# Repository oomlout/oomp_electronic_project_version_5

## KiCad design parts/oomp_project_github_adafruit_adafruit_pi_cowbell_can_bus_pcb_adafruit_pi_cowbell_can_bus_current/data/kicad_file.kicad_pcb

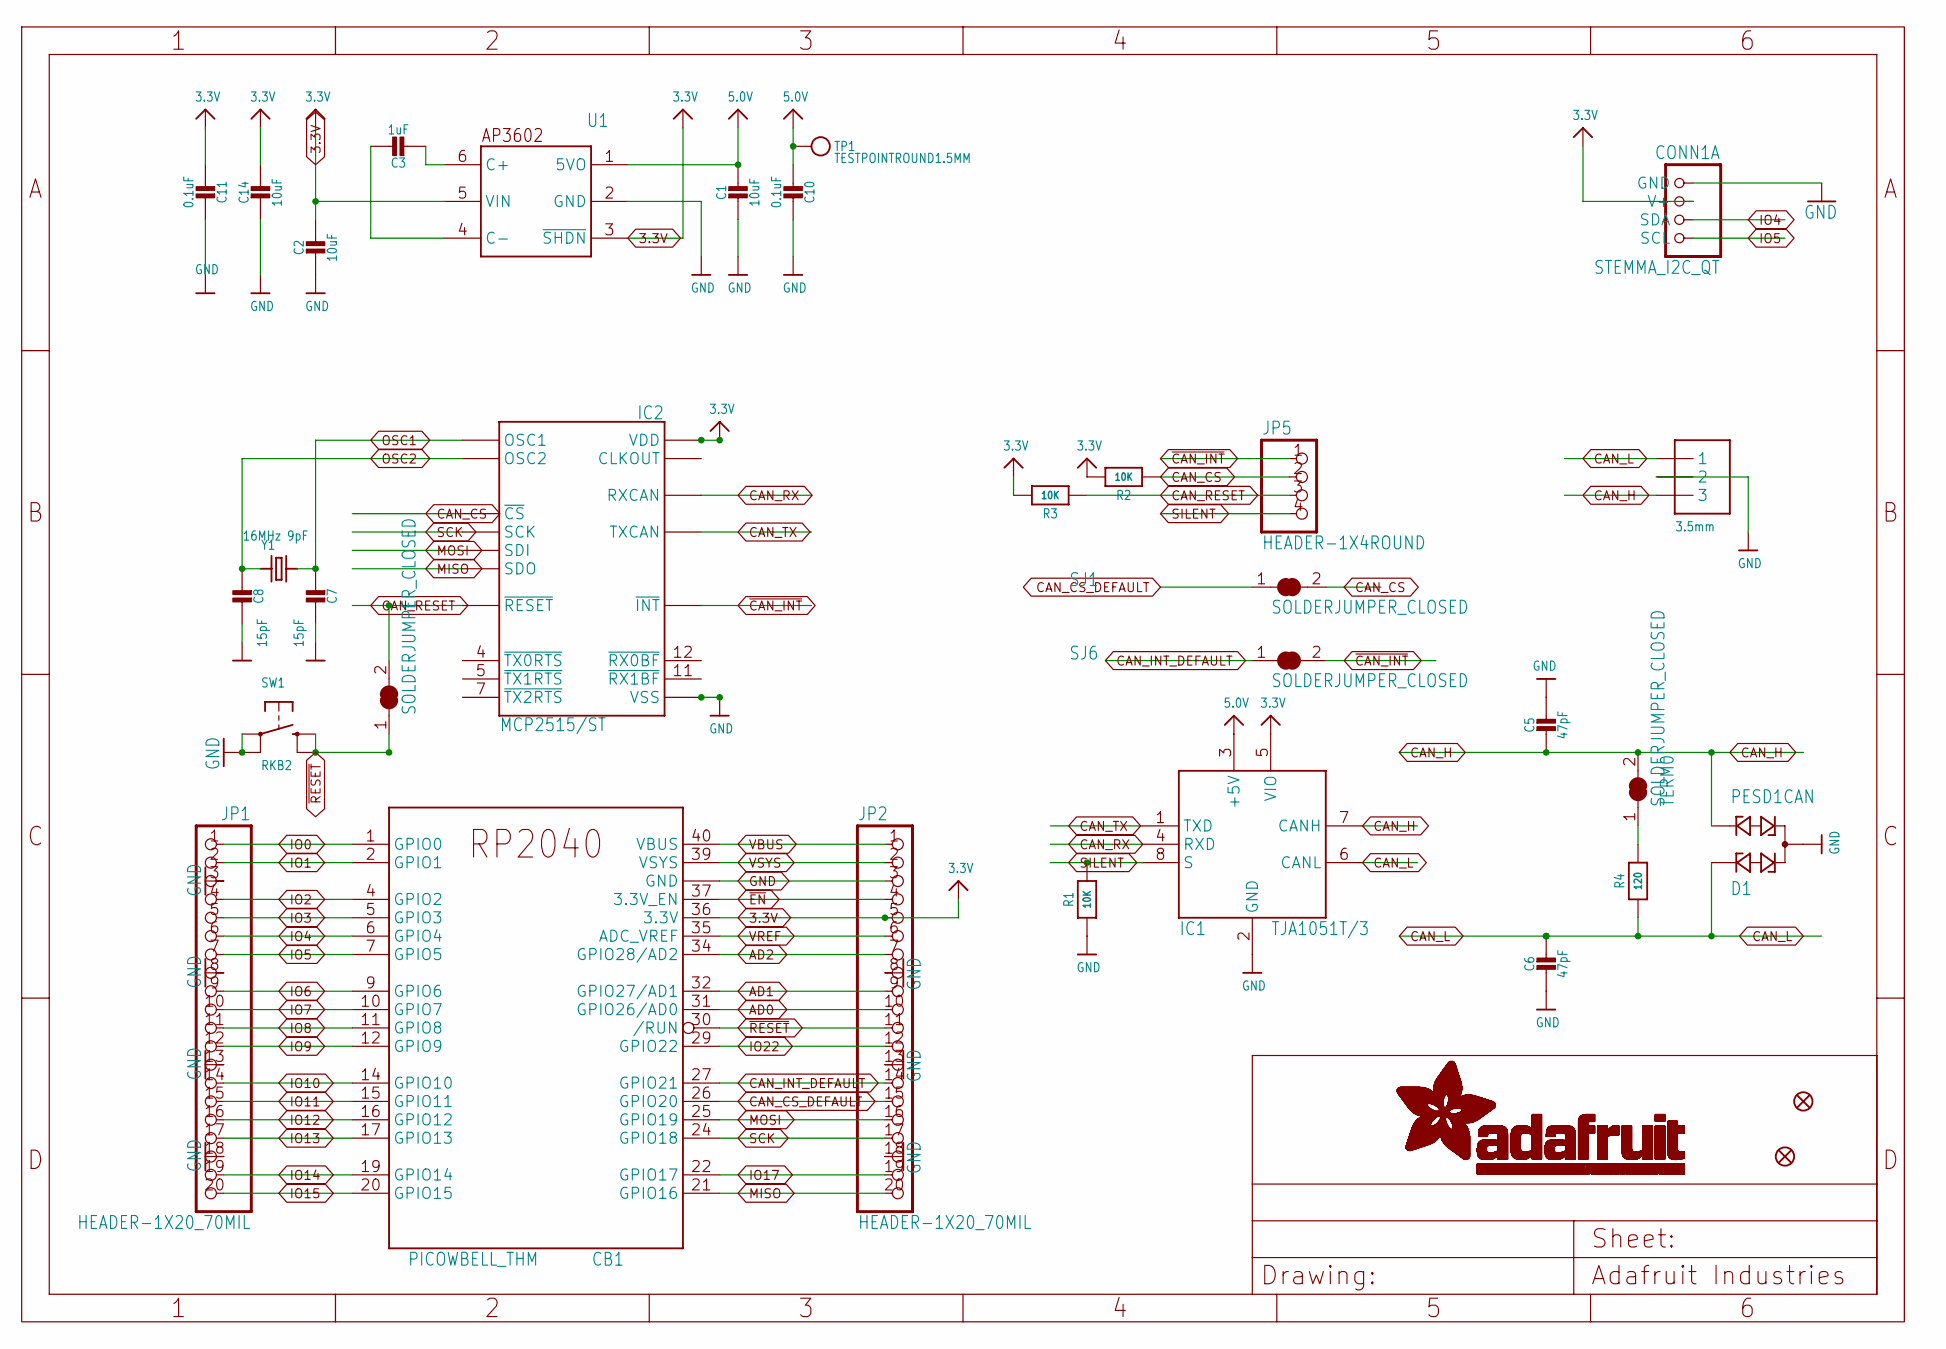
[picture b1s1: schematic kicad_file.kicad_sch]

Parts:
C1, C2, C14: 10uF; 0805-NO
C3: 1uF; 0805-NO
C5, C6: 47pF; 0603-NO
C7, C8: 15pF; 0603-NO
C10, C11: 0.1uF; 0603-NO
CAN0: 3.5mm; TERMBLOCK_1X3-3.5MM
CB1: PICOWBELL_THM
CONN1: STEMMA_I2C_QT; JST_SH4; LCSC C2845363
D1: PESD1CAN; SOT23
FID1, FID2: FIDUCIAL_1MM
IC1: TJA1051T/3; SOIC8_150MIL
IC2: MCP2515/ST; SSOP20
JP1, JP2: HEADER-1X20_70MIL; 1X20_ROUND_70MIL
JP5: HEADER-1X4ROUND; 1X04_ROUND
R1, R2, R3: 10K; 0603-NO
R4: 120; 0603-NO
SJ1, SJ5, SJ6: SOLDERJUMPER_CLOSED; SOLDERJUMPER_CLOSEDWIRE
SW1: RKB2; BTN_RKB2_4.6X2.8
TERM0: SOLDERJUMPER_CLOSED; SOLDERJUMPER_CLOSEDWIRE
TP1: TESTPOINTROUND1.5MM; TESTPOINT_ROUND_1.5MM
U1: AP3602; SOT23-6
Y1: 16MHz 9pF; CRYSTAL_3.2X2.5

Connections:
3.3V: C2.1, C11.2, C14.1, CB1.36 (3.3V), CONN1.2 (V+), IC1.5 (VIO), IC2.20 (VDD), JP2.5, R2.2, R3.2, U1.3 (~SHDN), U1.5 (VIN)
5.0V: C1.1, C10.2, IC1.3 (+5V), TP1.P$1, U1.1 (5VO)
AD0: CB1.31 (GPIO26/AD0), JP2.10
AD1: CB1.32 (GPIO27/AD1), JP2.9
AD2: CB1.34 (GPIO28/AD2), JP2.7
CAN_CS: IC2.18 (~CS), JP5.2, R2.1, SJ1.2
CAN_CS_DEFAULT: CB1.26 (GPIO20), JP2.15, SJ1.1
CAN_H: C5.2, CAN0.3, D1.2, IC1.7 (CANH), TERM0.2
CAN_INT_DEFAULT: CB1.27 (GPIO21), JP2.14, SJ6.1
CAN_L: C6.1, CAN0.1, D1.1, IC1.6 (CANL), R4.1
CAN_RESET: IC2.19 (~RESET), JP5.3, R3.1, SJ5.2
CAN_RX: IC1.4 (RXD), IC2.2 (RXCAN)
CAN_TX: IC1.1 (TXD), IC2.1 (TXCAN)
GND: C1.2, C2.2, C5.1, C6.2, C7.1, C8.1, C10.1, C11.1, C14.2, CAN0.2, CB1.3 (GND), CB1.8 (GND), CB1.13 (GND), CB1.18 (GND), CB1.23 (GND), CB1.28 (GND), CB1.33 (GND), CB1.38 (GND), CONN1.1 (GND), D1.3, IC1.2 (GND), IC2.10 (VSS), JP1.3, JP1.8, JP1.13, JP1.18, JP2.3, JP2.8, JP2.13, JP2.18, R1.1, SW1.A, SW1.A' (P1), U1.2 (GND)
IO0: CB1.1 (GPIO0), JP1.1
IO1: CB1.2 (GPIO1), JP1.2
IO2: CB1.4 (GPIO2), JP1.4
IO3: CB1.5 (GPIO3), JP1.5
IO4: CB1.6 (GPIO4), CONN1.3 (SDA), JP1.6
IO5: CB1.7 (GPIO5), CONN1.4 (SCL), JP1.7
IO6: CB1.9 (GPIO6), JP1.9
IO7: CB1.10 (GPIO7), JP1.10
IO8: CB1.11 (GPIO8), JP1.11
IO9: CB1.12 (GPIO9), JP1.12
IO10: CB1.14 (GPIO10), JP1.14
IO11: CB1.15 (GPIO11), JP1.15
IO12: CB1.16 (GPIO12), JP1.16
IO13: CB1.17 (GPIO13), JP1.17
IO14: CB1.19 (GPIO14), JP1.19
IO15: CB1.20 (GPIO15), JP1.20
IO17: CB1.22 (GPIO17), JP2.19
IO22: CB1.29 (GPIO22), JP2.12
MISO: CB1.21 (GPIO16), IC2.17 (SDO), JP2.20
MOSI: CB1.25 (GPIO19), IC2.16 (SDI), JP2.16
unnamed: C3.2, U1.6 (C+)
unnamed: C3.1, U1.4 (C-)
unnamed: R4.2, TERM0.1
OSC1: C7.2, IC2.9 (OSC1), Y1.2
OSC2: C8.2, IC2.8 (OSC2), Y1.1
SCK: CB1.24 (GPIO18), IC2.14 (SCK), JP2.17
SILENT: IC1.8 (S), JP5.4, R1.2
VBUS: CB1.40 (VBUS), JP2.1
VREF: CB1.35 (ADC_VREF), JP2.6
VSYS: CB1.39 (VSYS), JP2.2
~CAN_INT: IC2.13 (~INT), JP5.1, SJ6.2
~EN: CB1.37 (3.3V_EN), JP2.4
~RESET: CB1.30 (/RUN), JP2.11, SJ5.1, SW1.B (S), SW1.B' (S1)

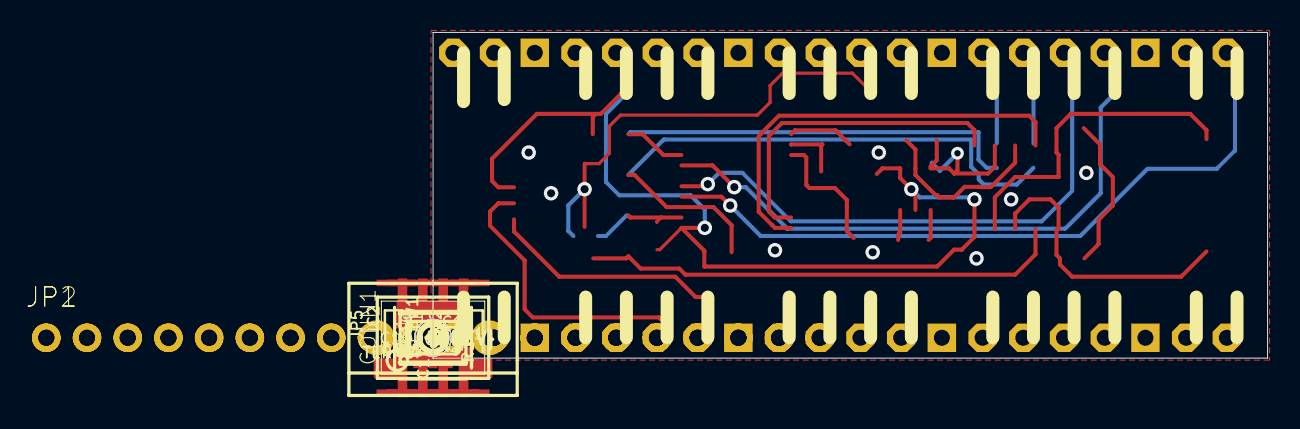
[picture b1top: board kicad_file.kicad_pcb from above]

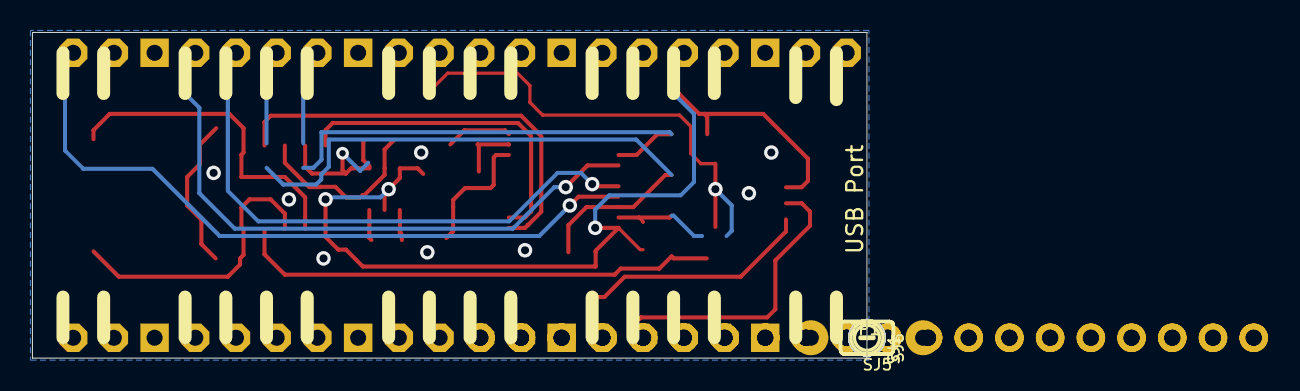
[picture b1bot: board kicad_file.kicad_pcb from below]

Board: 2 copper layers, 52.1 x 20.3 mm, 88 parts (43 on the bottom side), 47 nets.

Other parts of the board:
PLABEL36: PLABEL36
PLABEL37: PLABEL37
PLABEL38: PLABEL38
PLABEL40: PLABEL40
PLABEL41: PLABEL41
PLABEL42: PLABEL42
PLABEL43: PLABEL43
PLABEL44: PLABEL44
PLABEL45: PLABEL45
PLABEL46: PLABEL46
PLABEL47: PLABEL47
PLABEL49: PLABEL49
PLABEL50: PLABEL50
PLABEL51: PLABEL51
PLABEL52: PLABEL52
PLABEL53: PLABEL53
PLABEL54: PLABEL54
PLABEL55: PLABEL55
PLABEL56: PLABEL56
PLABEL57: PLABEL57
PLABEL58: PLABEL58
PLABEL59: PLABEL59
PLABEL60: PLABEL60
PLABEL61: PLABEL61
PLABEL62: PLABEL62
PLABEL63: PLABEL63
PLABEL64: PLABEL64
PLABEL65: PLABEL65
PLABEL66: PLABEL66
PLABEL67: PLABEL67
PLABEL68: PLABEL68
PLABEL69: PLABEL69
PLABEL70: PLABEL70
PLABEL71: PLABEL71
PLABEL72: PLABEL72
PLABEL73: PLABEL73
PLABEL74: PLABEL74
PLABEL75: PLABEL75
PLABEL76: PLABEL76
PLABEL77: PLABEL77
PLABEL78: PLABEL78
PLABEL79: PLABEL79
PLABEL80: PLABEL80
PLABEL81: PLABEL81
PLABEL82: PLABEL82
PLABEL83: PLABEL83
PLABEL84: PLABEL84
PLABEL85: PLABEL85
U$2, U$34: SYMBOL_MINUS
U$11: PCBFEAT-REV-040
UNK_HOLE_0: dummyfp0
UNK_HOLE_1: dummyfp1
UNK_HOLE_2: dummyfp2
UNK_HOLE_3: dummyfp3

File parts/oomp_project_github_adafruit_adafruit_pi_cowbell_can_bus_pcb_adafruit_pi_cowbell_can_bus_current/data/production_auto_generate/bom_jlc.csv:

Comment,Designator,Footprint,LCSC Part #
,JP5,Adafruit PiCowbell CAN Bus-import-fps:1X04_ROUND,C42431795
,"JP1,JP2",Adafruit PiCowbell CAN Bus-import-fps:1X20_ROUND_70MIL,C50981
,U$11,Adafruit PiCowbell CAN Bus-import-fps:PCBFEAT-REV-040,
,PLABEL36,Adafruit PiCowbell CAN Bus-import-fps:PLABEL36,
,PLABEL37,Adafruit PiCowbell CAN Bus-import-fps:PLABEL37,
,PLABEL38,Adafruit PiCowbell CAN Bus-import-fps:PLABEL38,
,PLABEL40,Adafruit PiCowbell CAN Bus-import-fps:PLABEL40,
,PLABEL41,Adafruit PiCowbell CAN Bus-import-fps:PLABEL41,
,PLABEL42,Adafruit PiCowbell CAN Bus-import-fps:PLABEL42,
,PLABEL43,Adafruit PiCowbell CAN Bus-import-fps:PLABEL43,
,PLABEL44,Adafruit PiCowbell CAN Bus-import-fps:PLABEL44,
,PLABEL45,Adafruit PiCowbell CAN Bus-import-fps:PLABEL45,
,PLABEL46,Adafruit PiCowbell CAN Bus-import-fps:PLABEL46,
,PLABEL47,Adafruit PiCowbell CAN Bus-import-fps:PLABEL47,
,PLABEL49,Adafruit PiCowbell CAN Bus-import-fps:PLABEL49,
,PLABEL50,Adafruit PiCowbell CAN Bus-import-fps:PLABEL50,
,PLABEL51,Adafruit PiCowbell CAN Bus-import-fps:PLABEL51,
,PLABEL52,Adafruit PiCowbell CAN Bus-import-fps:PLABEL52,
,PLABEL53,Adafruit PiCowbell CAN Bus-import-fps:PLABEL53,
,PLABEL54,Adafruit PiCowbell CAN Bus-import-fps:PLABEL54,
,PLABEL55,Adafruit PiCowbell CAN Bus-import-fps:PLABEL55,
,PLABEL56,Adafruit PiCowbell CAN Bus-import-fps:PLABEL56,
,PLABEL57,Adafruit PiCowbell CAN Bus-import-fps:PLABEL57,
,PLABEL58,Adafruit PiCowbell CAN Bus-import-fps:PLABEL58,
,PLABEL59,Adafruit PiCowbell CAN Bus-import-fps:PLABEL59,
,PLABEL60,Adafruit PiCowbell CAN Bus-import-fps:PLABEL60,
,PLABEL61,Adafruit PiCowbell CAN Bus-import-fps:PLABEL61,
,PLABEL62,Adafruit PiCowbell CAN Bus-import-fps:PLABEL62,
,PLABEL63,Adafruit PiCowbell CAN Bus-import-fps:PLABEL63,
,PLABEL64,Adafruit PiCowbell CAN Bus-import-fps:PLABEL64,
,PLABEL65,Adafruit PiCowbell CAN Bus-import-fps:PLABEL65,
,PLABEL66,Adafruit PiCowbell CAN Bus-import-fps:PLABEL66,
,PLABEL67,Adafruit PiCowbell CAN Bus-import-fps:PLABEL67,
,PLABEL68,Adafruit PiCowbell CAN Bus-import-fps:PLABEL68,
,PLABEL69,Adafruit PiCowbell CAN Bus-import-fps:PLABEL69,
,PLABEL70,Adafruit PiCowbell CAN Bus-import-fps:PLABEL70,
,PLABEL71,Adafruit PiCowbell CAN Bus-import-fps:PLABEL71,
,PLABEL72,Adafruit PiCowbell CAN Bus-import-fps:PLABEL72,
,PLABEL73,Adafruit PiCowbell CAN Bus-import-fps:PLABEL73,
,PLABEL74,Adafruit PiCowbell CAN Bus-import-fps:PLABEL74,
,PLABEL75,Adafruit PiCowbell CAN Bus-import-fps:PLABEL75,
,PLABEL76,Adafruit PiCowbell CAN Bus-import-fps:PLABEL76,
,PLABEL77,Adafruit PiCowbell CAN Bus-import-fps:PLABEL77,
,PLABEL78,Adafruit PiCowbell CAN Bus-import-fps:PLABEL78,
,PLABEL79,Adafruit PiCowbell CAN Bus-import-fps:PLABEL79,
,PLABEL80,Adafruit PiCowbell CAN Bus-import-fps:PLABEL80,
,PLABEL81,Adafruit PiCowbell CAN Bus-import-fps:PLABEL81,
,PLABEL82,Adafruit PiCowbell CAN Bus-import-fps:PLABEL82,
,PLABEL83,Adafruit PiCowbell CAN Bus-import-fps:PLABEL83,
,PLABEL84,Adafruit PiCowbell CAN Bus-import-fps:PLABEL84,
,PLABEL85,Adafruit PiCowbell CAN Bus-import-fps:PLABEL85,
,TERM0,Adafruit PiCowbell CAN Bus-import-fps:SOLDERJUMPER_CLOSEDWIRE,
,"U$2,U$34",Adafruit PiCowbell CAN Bus-import-fps:SYMBOL_MINUS,
,TP1,Adafruit PiCowbell CAN Bus-import-fps:TESTPOINT_ROUND_1.5MM,
0.1uF,"C10,C11",Adafruit PiCowbell CAN Bus-import-fps:0603-NO,C14663
10K,"R1,R2,R3",Adafruit PiCowbell CAN Bus-import-fps:0603-NO,C98220
10uF,"C1,C2,C14",Adafruit PiCowbell CAN Bus-import-fps:0805-NO,
120,R4,Adafruit PiCowbell CAN Bus-import-fps:0603-NO,C2906988
15pF,"C7,C8",Adafruit PiCowbell CAN Bus-import-fps:0603-NO,
16MHz 9pF,Y1,Adafruit PiCowbell CAN Bus-import-fps:CRYSTAL_3.2X2.5,
1uF,C3,Adafruit PiCowbell CAN Bus-import-fps:0805-NO,
3.5mm,CAN0,Adafruit PiCowbell CAN Bus-import-fps:TERMBLOCK_1X3-3.5MM,
47pF,"C5,C6",Adafruit PiCowbell CAN Bus-import-fps:0603-NO,C105622
AP3602,U1,Adafruit PiCowbell CAN Bus-import-fps:SOT23-6,
MCP2515/ST,IC2,Adafruit PiCowbell CAN Bus-import-fps:SSOP20,
PESD1CAN,D1,Adafruit PiCowbell CAN Bus-import-fps:SOT23,
PICOWBELL_THM,CB1,Adafruit PiCowbell CAN Bus-import-fps:PICOWBELL_THM,
RKB2,SW1,Adafruit PiCowbell CAN Bus-import-fps:BTN_RKB2_4.6X2.8,
STEMMA_I2C_QT,CONN1,Adafruit PiCowbell CAN Bus-import-fps:JST_SH4,C160404
TJA1051T/3,IC1,Adafruit PiCowbell CAN Bus-import-fps:SOIC8_150MIL,

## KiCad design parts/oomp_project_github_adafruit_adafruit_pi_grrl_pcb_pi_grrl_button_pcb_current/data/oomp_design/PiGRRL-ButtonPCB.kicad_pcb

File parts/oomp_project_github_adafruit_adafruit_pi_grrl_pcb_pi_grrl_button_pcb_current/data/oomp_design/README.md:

# OOMP KiCad design copy

Open `PiGRRL-ButtonPCB.kicad_pro` (or the `.kicad_pcb` / `.kicad_sch`) in KiCad. Local OOMP libraries are under `libraries/`. Original inputs are preserved in [../original/](../original/).

Only verified unchanged installed KiCad defaults were renamed. Modified, custom, unmatched and unavailable items remain unchanged. Soldering variants are never swapped during conversion. Existing pad coordinates, nets and UUIDs are preserved.

See [conversion_report.yaml](conversion_report.yaml) for every conversion and skip. Copy this directory before editing; regeneration refuses to overwrite edited design files.

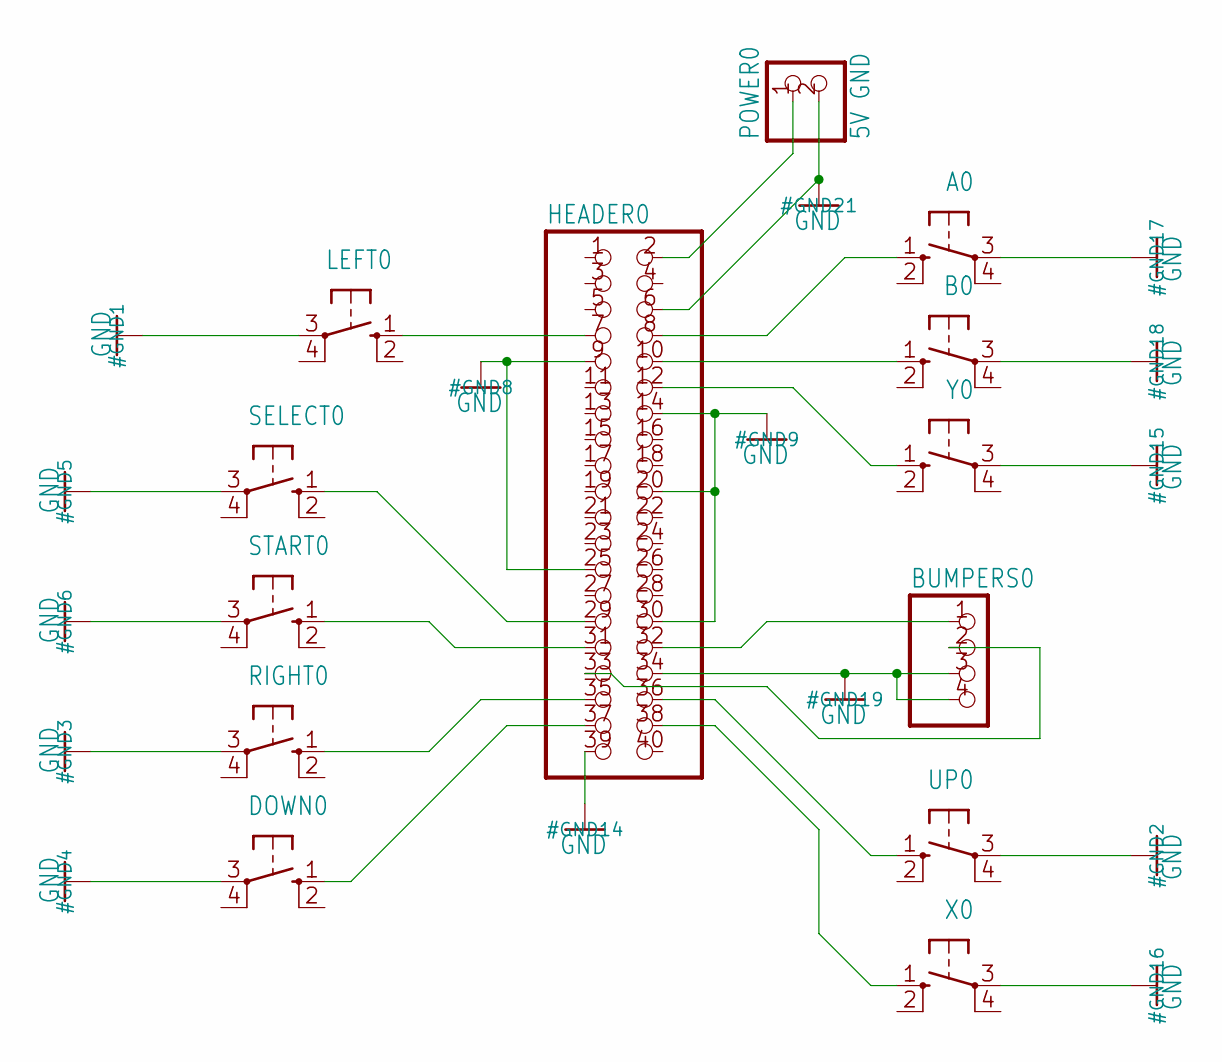
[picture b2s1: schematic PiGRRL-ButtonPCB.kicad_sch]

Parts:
A0: 10-XX; B3F-10XX; MPN B3F-1000
B0: 10-XX; B3F-10XX; MPN B3F-1000
BUMPERS0: PINHD-1X4; 1X04
DOWN0: 10-XX; B3F-10XX; MPN B3F-1000
HEADER0: PINHD-2X20; 2X20
LEFT0: 10-XX; B3F-10XX; MPN B3F-1000
POWER0: 5V GND; 1X02
RIGHT0: 10-XX; B3F-10XX; MPN B3F-1000
SELECT0: 10-XX; B3F-10XX; MPN B3F-1000
START0: 10-XX; B3F-10XX; MPN B3F-1000
UP0: 10-XX; B3F-10XX; MPN B3F-1000
X0: 10-XX; B3F-10XX; MPN B3F-1000
Y0: 10-XX; B3F-10XX; MPN B3F-1000

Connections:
+5V: HEADER0.2, POWER0.1
GND: A0.3, B0.3, BUMPERS0.3, BUMPERS0.4, DOWN0.3, HEADER0.6, HEADER0.9, HEADER0.14, HEADER0.20, HEADER0.25, HEADER0.30, HEADER0.34, HEADER0.39, LEFT0.3, POWER0.2, RIGHT0.3, SELECT0.3, START0.3, UP0.3, X0.3, Y0.3
unnamed: HEADER0.7, LEFT0.1 (S)
unnamed: HEADER0.36, UP0.1 (S)
unnamed: HEADER0.12, Y0.1 (S)
unnamed: HEADER0.35, RIGHT0.1 (S)
unnamed: DOWN0.1 (S), HEADER0.37
unnamed: HEADER0.38, X0.1 (S)
unnamed: A0.1 (S), HEADER0.8
unnamed: B0.1 (S), HEADER0.10
unnamed: HEADER0.29, SELECT0.1 (S)
unnamed: HEADER0.31, START0.1 (S)
unnamed: BUMPERS0.1, HEADER0.32
unnamed: BUMPERS0.2, HEADER0.33

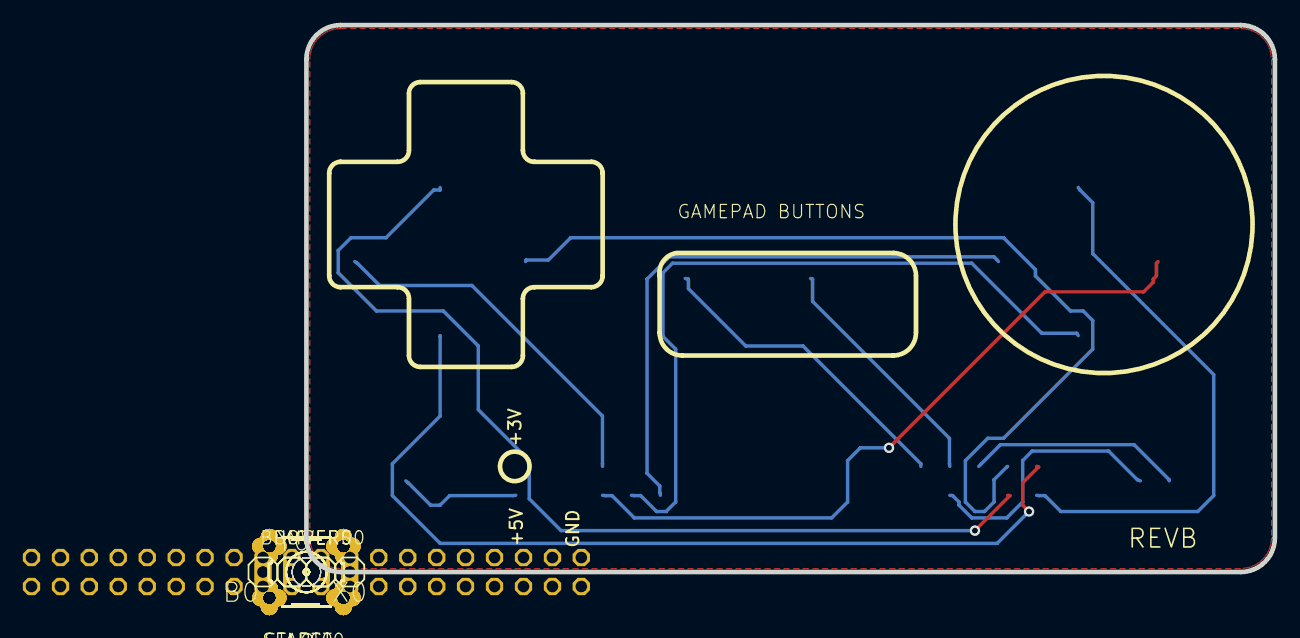
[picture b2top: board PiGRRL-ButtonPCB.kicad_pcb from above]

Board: 2 copper layers, 85.0 x 48.0 mm, 17 parts (1 on the bottom side), 14 nets.

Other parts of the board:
UNK_HOLE_0: dummyfp0
UNK_HOLE_1: dummyfp1
UNK_HOLE_2: dummyfp2
UNK_HOLE_3: dummyfp3

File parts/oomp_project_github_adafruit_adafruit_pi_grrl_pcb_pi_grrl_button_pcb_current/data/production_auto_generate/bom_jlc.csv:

Comment,Designator,Footprint,LCSC Part #
,BUMPERS0,PiGRRL-ButtonPCB-import-fps:1X04,C42431795
,HEADER0,PiGRRL-ButtonPCB-import-fps:2X20,
,"A0,B0,DOWN0,LEFT0,RIGHT0,SELECT0,START0,UP0,X0,Y0",PiGRRL-ButtonPCB-import-fps:B3F-10XX,
5V GND,POWER0,PiGRRL-ButtonPCB-import-fps:1X02,C492401

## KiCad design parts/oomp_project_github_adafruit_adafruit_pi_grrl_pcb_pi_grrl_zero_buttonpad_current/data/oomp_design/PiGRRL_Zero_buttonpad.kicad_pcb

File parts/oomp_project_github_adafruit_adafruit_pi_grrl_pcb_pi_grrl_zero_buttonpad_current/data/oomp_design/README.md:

# OOMP KiCad design copy

Open `PiGRRL_Zero_buttonpad.kicad_pro` (or the `.kicad_pcb` / `.kicad_sch`) in KiCad. Local OOMP libraries are under `libraries/`. Original inputs are preserved in [../original/](../original/).

Only verified unchanged installed KiCad defaults were renamed. Modified, custom, unmatched and unavailable items remain unchanged. Soldering variants are never swapped during conversion. Existing pad coordinates, nets and UUIDs are preserved.

See [conversion_report.yaml](conversion_report.yaml) for every conversion and skip. Copy this directory before editing; regeneration refuses to overwrite edited design files.

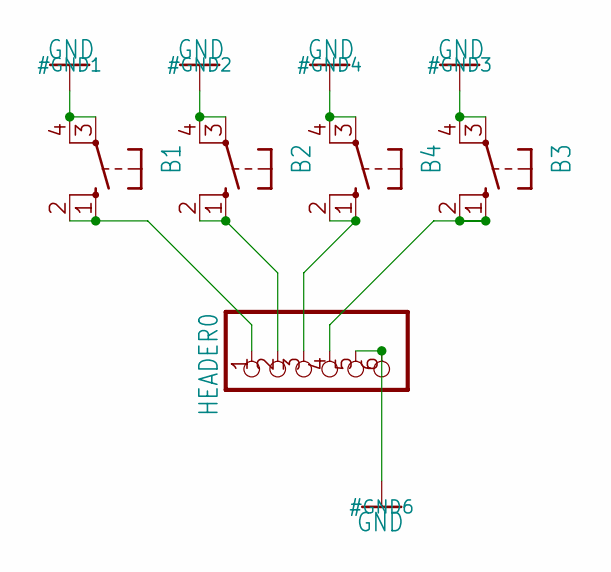
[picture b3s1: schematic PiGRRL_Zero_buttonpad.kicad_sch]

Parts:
B1, B2, B3, B4: 10-XX; B3F-10XX; MPN B3F-1000
HEADER0: PINHD-1X6; 1X06

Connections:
GND: B1.3, B1.4 (P1), B2.3, B2.4 (P1), B3.3, B3.4 (P1), B4.3, B4.4 (P1), HEADER0.5, HEADER0.6
unnamed: B1.1 (S), B1.2 (S1), HEADER0.1
unnamed: B2.1 (S), B2.2 (S1), HEADER0.2
unnamed: B3.1 (S), B3.2 (S1), HEADER0.4
unnamed: B4.1 (S), B4.2 (S1), HEADER0.3

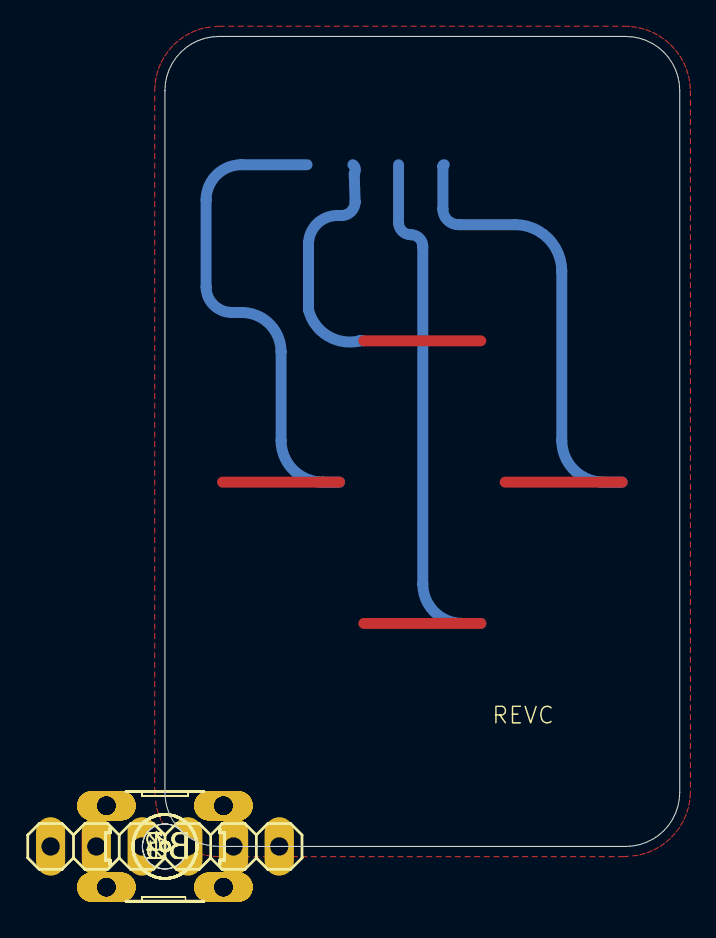
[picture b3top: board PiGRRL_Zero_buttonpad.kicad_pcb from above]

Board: 16 copper layers, 28.6 x 45.0 mm, 7 parts (0 on the bottom side), 5 nets.

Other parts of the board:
UNK_HOLE_0: dummyfp0
UNK_HOLE_1: dummyfp1

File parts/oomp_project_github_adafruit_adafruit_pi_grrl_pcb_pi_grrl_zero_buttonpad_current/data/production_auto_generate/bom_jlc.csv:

Comment,Designator,Footprint,LCSC Part #
,HEADER0,PiGRRL_Zero_buttonpad-import-fps:1X06,C37208
,"B1,B2,B3,B4",PiGRRL_Zero_buttonpad-import-fps:B3F-10XX,

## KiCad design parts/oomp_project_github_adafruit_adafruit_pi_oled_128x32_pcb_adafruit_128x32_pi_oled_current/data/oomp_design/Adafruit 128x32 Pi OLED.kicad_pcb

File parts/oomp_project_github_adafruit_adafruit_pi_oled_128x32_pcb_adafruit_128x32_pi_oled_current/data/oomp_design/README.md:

# OOMP KiCad design copy

Open `Adafruit 128x32 Pi OLED.kicad_pro` (or the `.kicad_pcb` / `.kicad_sch`) in KiCad. Local OOMP libraries are under `libraries/`. Original inputs are preserved in [../original/](../original/).

Only verified unchanged installed KiCad defaults were renamed. Modified, custom, unmatched and unavailable items remain unchanged. Soldering variants are never swapped during conversion. Existing pad coordinates, nets and UUIDs are preserved.

See [conversion_report.yaml](conversion_report.yaml) for every conversion and skip. Copy this directory before editing; regeneration refuses to overwrite edited design files.

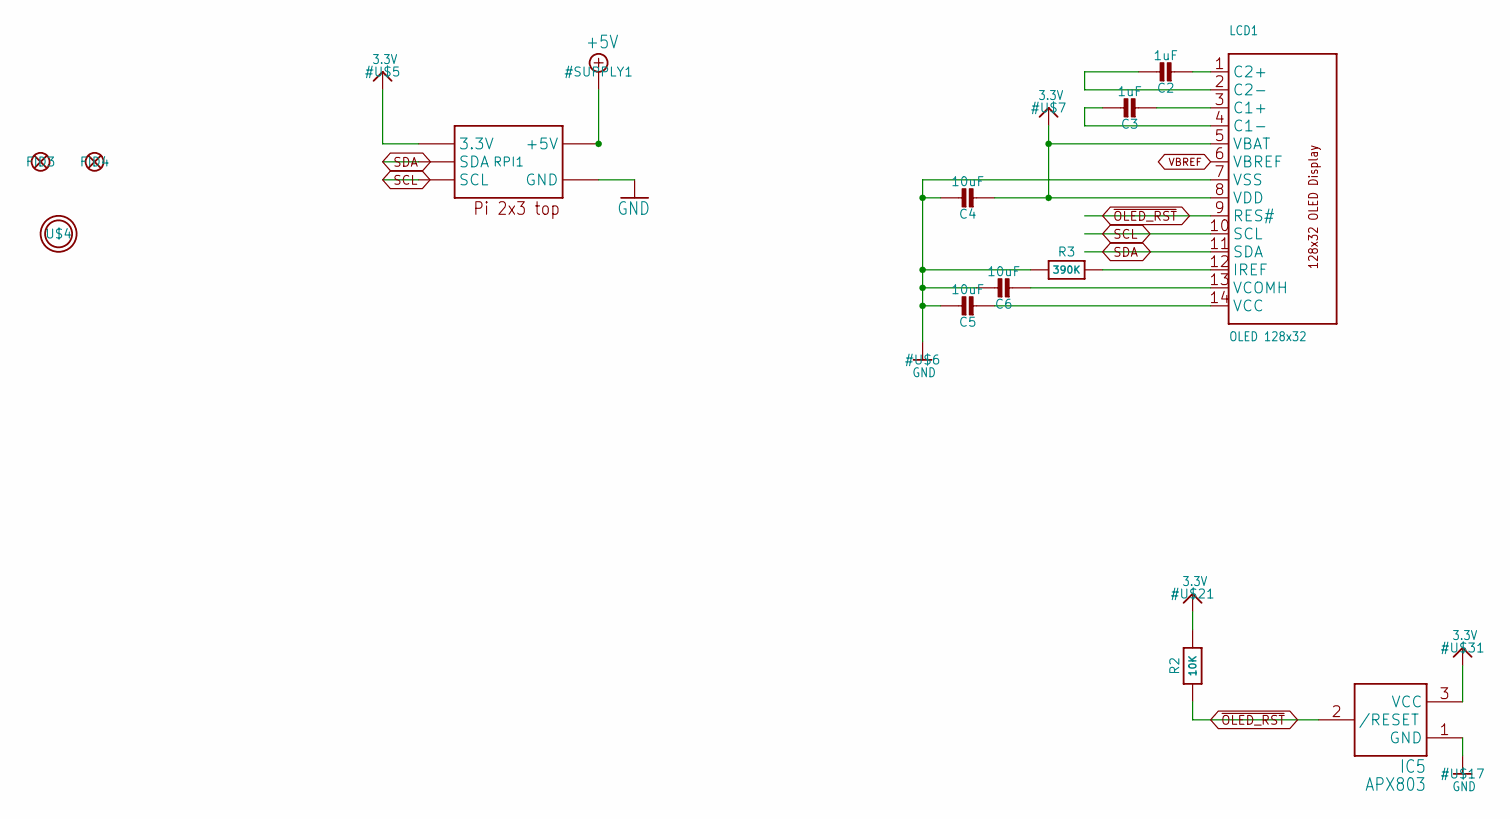
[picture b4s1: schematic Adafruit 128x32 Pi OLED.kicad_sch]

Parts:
C2, C3: 1uF; 0805-NO
C4, C5, C6: 10uF; 0805-NO
FID3, FID4: FIDUCIAL_1MM
IC5: APX803; SOT23
LCD1: OLED 128x32; UG-2832HSWEG02_WRAPUNDER
R2: 10K; 0805-NO
R3: 390K; 0805-NO
RPI1: RASPBERRYPI_2X3; RASPBERRYPI_2X3_THMSMT
U$4: MOUNTINGHOLE3.0THIN; MOUNTINGHOLE_3.0_PLATEDTHIN

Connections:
3.3V: C4.2, IC5.3 (VCC), LCD1.5 (VBAT), LCD1.8 (VDD), R2.2, RPI1.1 (3.3V), RPI1.1' (3.3V)
+5V: RPI1.2 (+5V), RPI1.2' (+5V), RPI1.4 (+5V), RPI1.4' (+5V)
GND: C4.1, C5.1, C6.1, IC5.1 (GND), LCD1.7 (VSS), R3.1, RPI1.6 (GND), RPI1.6' (GND)
unnamed: C2.2, LCD1.1 (C2+)
unnamed: C2.1, LCD1.2 (C2-)
unnamed: C3.2, LCD1.3 (C1+)
unnamed: C3.1, LCD1.4 (C1-)
unnamed: C6.2, LCD1.13 (VCOMH)
unnamed: C5.2, LCD1.14 (VCC)
unnamed: LCD1.12 (IREF), R3.2
SCL: LCD1.10 (SCL), RPI1.5 (SCL), RPI1.5' (SCL)
SDA: LCD1.11 (SDA), RPI1.3 (SDA), RPI1.3' (SDA)
VBREF: LCD1.6 (VBREF)
~OLED_RST: IC5.2 (/RESET), LCD1.9 (RES#), R2.1

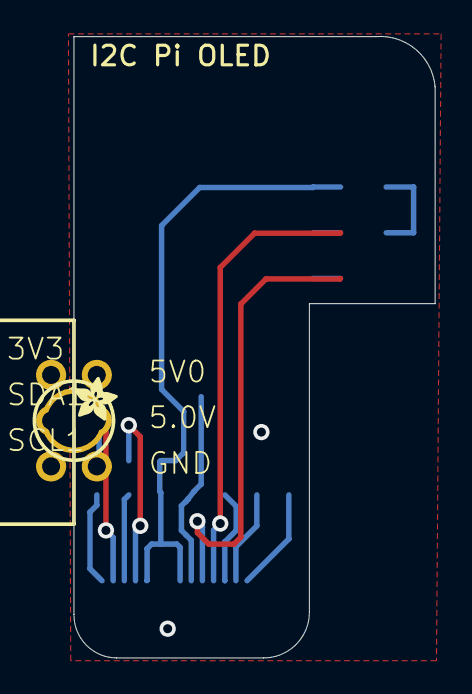
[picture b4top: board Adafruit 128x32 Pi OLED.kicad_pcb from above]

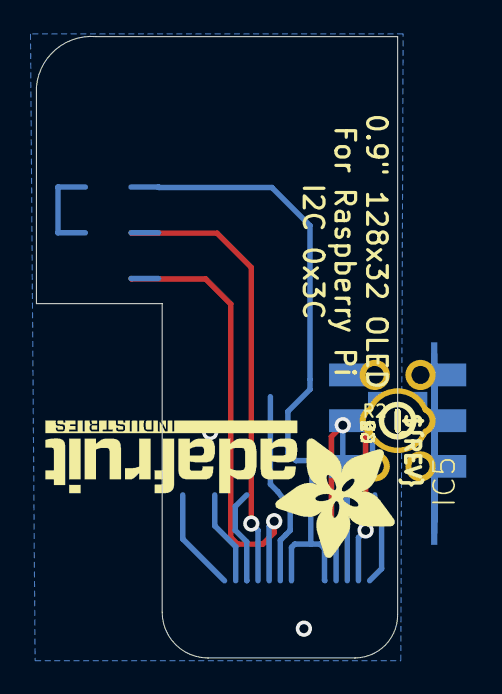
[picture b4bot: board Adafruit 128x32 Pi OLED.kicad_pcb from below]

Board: 16 copper layers, 20.1 x 34.5 mm, 16 parts (12 on the bottom side), 13 nets.

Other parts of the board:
U$1: ADAFRUIT_2.5MM
U$3: PCBFEAT-REV-040
U$8: ADAFRUIT_TEXT_20MM

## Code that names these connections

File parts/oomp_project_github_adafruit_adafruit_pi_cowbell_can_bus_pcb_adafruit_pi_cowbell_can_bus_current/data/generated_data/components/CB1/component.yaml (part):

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    dnp: false
    pins:
    - number: '1'
      name: GPIO0
      electrical_type: bidirectional
      graphic_style: line
      local_position:
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        pin_number: '1'
        pin_name: '1'
    - number: '2'
      name: GPIO1
      electrical_type: bidirectional
      graphic_style: line
      local_position:
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        pin_number: '2'
        pin_name: GND
    - number: '4'
      name: GPIO2
      electrical_type: bidirectional
      graphic_style: line
      local_position:
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        pin_number: '4'
        pin_name: '4'
    - number: '5'
      name: GPIO3
      electrical_type: bidirectional
      graphic_style: line
      local_position:
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        pin_number: '5'
        pin_name: '5'
    - number: '6'
      name: GPIO4
      electrical_type: bidirectional
      graphic_style: line
      local_position:
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        pin_number: '6'
        pin_name: '6'
    - number: '7'
      name: GPIO5
      electrical_type: bidirectional
      graphic_style: line
      local_position:
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        pin_number: '2'
        pin_name: GND
    - number: '9'
      name: GPIO6
      electrical_type: bidirectional
      graphic_style: line
      local_position:
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        pin_number: '9'
        pin_name: '9'
    - number: '10'
      name: GPIO7
      electrical_type: bidirectional
      graphic_style: line
      local_position:
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        pin_number: '10'
        pin_name: '10'
    - number: '11'
      name: GPIO8
      electrical_type: bidirectional
      graphic_style: line
      local_position:
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        pin_number: '11'
        pin_name: '11'
    - number: '12'
      name: GPIO9
      electrical_type: bidirectional
      graphic_style: line
      local_position:
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        pin_number: '2'
        pin_name: GND
    - number: '14'
      name: GPIO10
      electrical_type: bidirectional
      graphic_style: line
      local_position:
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        pin_number: '14'
        pin_name: '14'
    - number: '15'
      name: GPIO11
      electrical_type: bidirectional
      graphic_style: line
      local_position:
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        pin_number: '15'
        pin_name: '15'
    - number: '16'
      name: GPIO12
      electrical_type: bidirectional
      graphic_style: line
      local_position:
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        pin_number: '16'
        pin_name: '16'
    - number: '17'
      name: GPIO13
      electrical_type: bidirectional
      graphic_style: line
      local_position:
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        pin_number: '2'
        pin_name: GND
    - number: '19'
      name: GPIO14
      electrical_type: bidirectional
      graphic_style: line
      local_position:
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        pin_number: '19'
        pin_name: '19'
    - number: '20'
      name: GPIO15
      electrical_type: bidirectional
      graphic_style: line
      local_position:
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        pin_number: '20'
        pin_name: '20'
    - number: '21'
      name: GPIO16
      electrical_type: bidirectional
      graphic_style: line
      local_position:
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        pin_number: '20'
        pin_name: '20'
    - number: '22'
      name: GPIO17
      electrical_type: bidirectional
      graphic_style: line
      local_position:
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        pin_number: '2'
        pin_name: GND
    - number: '24'
      name: GPIO18
      electrical_type: bidirectional
      graphic_style: line
      local_position:
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        pin_number: '17'
        pin_name: '17'
    - number: '25'
      name: GPIO19
      electrical_type: bidirectional
      graphic_style: line
      local_position:
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        pin_number: '16'
        pin_name: '16'
    - number: '26'
      name: GPIO20
      electrical_type: bidirectional
      graphic_style: line
      local_position:
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        pin_number: '1'
        pin_name: '1'
    - number: '27'
      name: GPIO21
      electrical_type: bidirectional
      graphic_style: line
      local_position:
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        pin_number: '2'
        pin_name: GND
    - number: '29'
      name: GPIO22
      electrical_type: bidirectional
      graphic_style: line
      local_position:
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        pin_number: B'
        pin_name: S1
    - number: '31'
      name: GPIO26/AD0
      electrical_type: bidirectional
      graphic_style: line
      local_position:
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        pin_number: '10'
        pin_name: '10'
    - number: '32'
      name: GPIO27/AD1
      electrical_type: bidirectional
      graphic_style: line
      local_position:
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        pin_number: '2'
        pin_name: GND
    - number: '34'
      name: GPIO28/AD2
      electrical_type: bidirectional
      graphic_style: line
      local_position:
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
